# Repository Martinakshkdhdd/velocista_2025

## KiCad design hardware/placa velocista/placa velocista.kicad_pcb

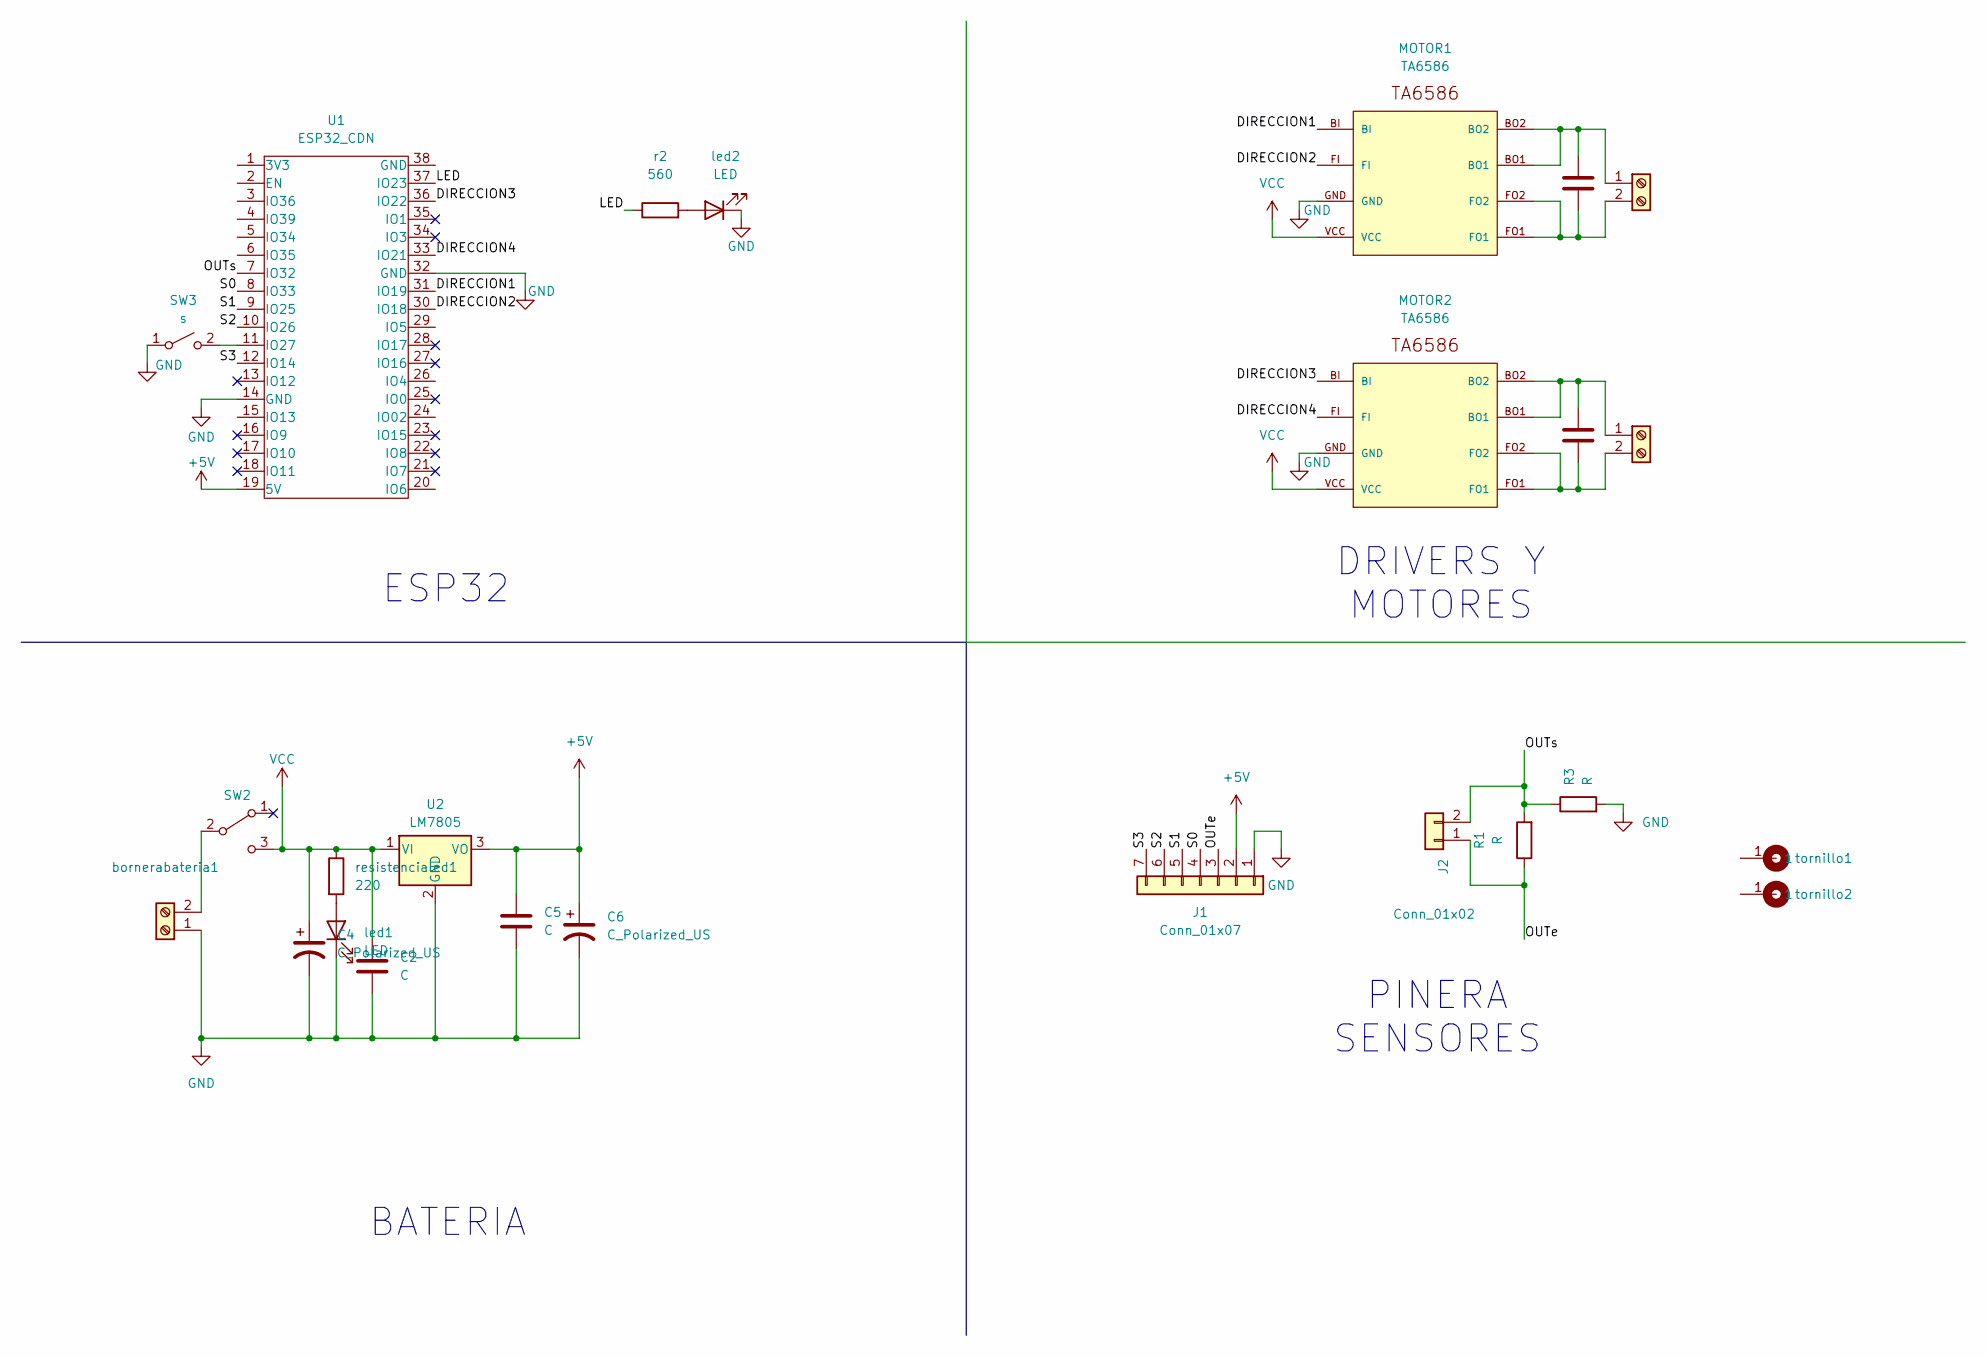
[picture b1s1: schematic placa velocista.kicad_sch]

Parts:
C2, C5, C7, C11: C; C_Disc_D5.0mm_W2.5mm_P5.00mm
C4, C6: C_Polarized_US; CP_Radial_D10.0mm_P3.50mm
J1: Conn_01x07; PinSocket_1x07_P2.00mm_Vertical
J2: Conn_01x02; PinHeader_1x02_P2.54mm_Vertical
J5: Screw_Terminal_01x02; BORNERA2
MOTOR1, MOTOR2: TA6586; TA6586-FOOTPRINT
R1, R3: R; R_0805
SW2: SW_SPDT; SW_SPDT_TH_Vertical
SW3: s; SW_PUSH_6mm
U1: ESP32_CDN; ESP32_DEVKITC
U2: LM7805; TO-220-3_Vertical
bormo1: Screw_Terminal_01x02; BORNERA2
bornerabateria1: bornera; BORNERA2
led1, led2: LED; LED_D5.0mm
r2: 560; RES0.3
resistencialed1: 220; RES0.3
tornillo1, tornillo2: Cable_PAD; Tornillo_M3_8mm

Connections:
+5V: C5.1, C6.1, J1.2, U1.19 (5V), U2.3 (VO)
/DIRECCION1: MOTOR1.BI, U1.31 (IO19)
/DIRECCION2: MOTOR1.FI, U1.30 (IO18)
/DIRECCION3: MOTOR2.BI, U1.36 (IO22)
/DIRECCION4: MOTOR2.FI, U1.33 (IO21)
/LED: U1.37 (IO23), r2.1
/OUTe: J1.3, J2.1, R1.1
/OUTs: J2.2, R1.2, R3.1, U1.7 (IO32)
/S0: J1.4, U1.8 (IO33)
/S1: J1.5, U1.9 (IO25)
/S2: J1.6, U1.10 (IO26)
/S3: J1.7, U1.12 (IO14)
GND: C2.2, C4.2, C5.2, C6.2, J1.1, MOTOR1.GND, MOTOR2.GND, R3.2, SW3.1 (A), U1.14 (GND), U1.32 (GND), U2.2 (GND), bornerabateria1.1, led1.1 (K), led2.1 (K)
unnamed: C7.1, J5.1, MOTOR1.BO1, MOTOR1.BO2
unnamed: C7.2, J5.2, MOTOR1.FO1, MOTOR1.FO2
unnamed: SW2.2 (B), bornerabateria1.2
unnamed: SW3.2 (B), U1.11 (IO27)
unnamed: C11.1, MOTOR2.BO1, MOTOR2.BO2, bormo1.1
unnamed: C11.2, MOTOR2.FO1, MOTOR2.FO2, bormo1.2
unnamed: led1.2 (A), resistencialed1.2
unnamed: led2.2 (A), r2.2
VCC: C2.1, C4.1, MOTOR1.VCC, MOTOR2.VCC, SW2.3 (C), U2.1 (VI), resistencialed1.1

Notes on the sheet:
ESP32
DRIVERS Y MOTORES
PINERA SENSORES
BATERIA

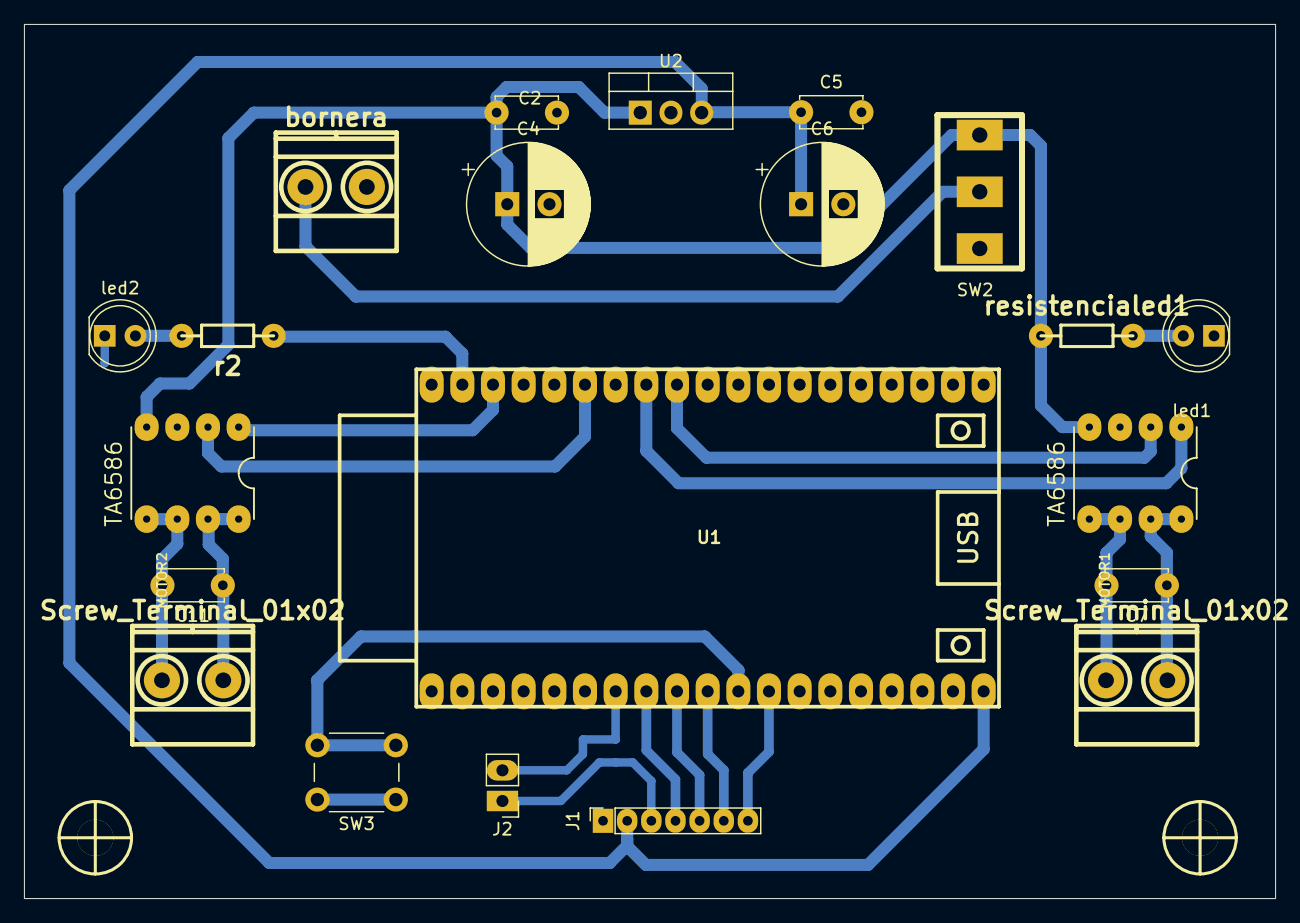
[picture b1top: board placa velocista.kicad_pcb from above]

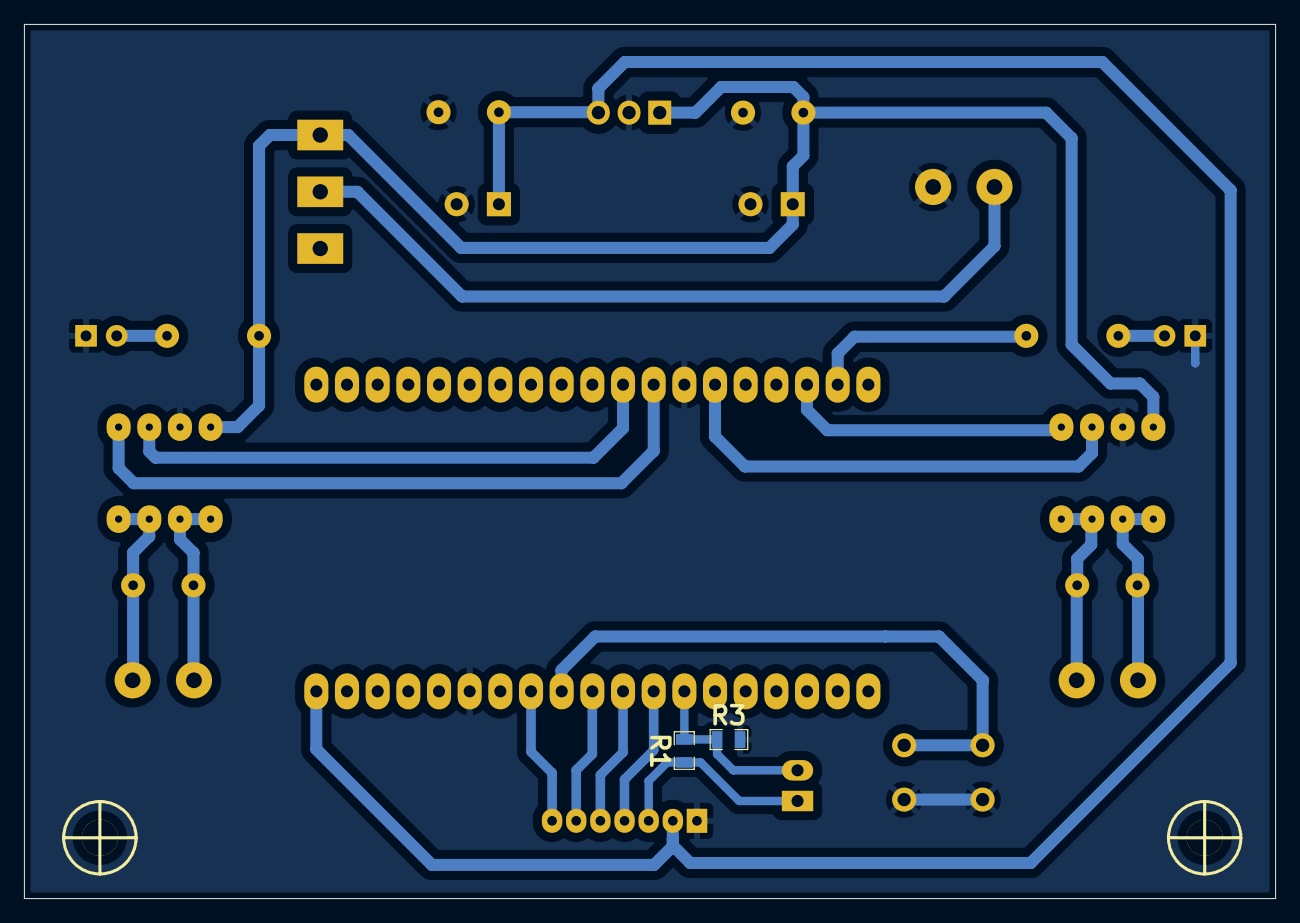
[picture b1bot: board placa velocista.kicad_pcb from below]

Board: 2 copper layers, 103.6 x 72.4 mm, 25 parts (2 on the bottom side), 22 nets.

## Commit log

2025-05-20 robot velocista
2025-05-20 cambio de gnd prueba
2025-06-25 Actualizacion de placa
2025-06-25 Agregue divisor de tension
2025-07-10 Diseño 3d añadido
